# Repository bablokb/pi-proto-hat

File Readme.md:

Pi-Proto-Hat
============

This is a PCB design for a Pi-sized prototyping hat:

The hat has a 40-pin connector for the Pi and exposes most of the GPIOs
on the top and bottom edge. On the left side you will find two connectors
for I2C and one for the UART-pins.

In the middle of the pcb there are two rows with power (5V and 3.3V) and
GND. The pins of the prototyping areas above and below the power-rails
are not connected.

In the directory `kicad/pi-proto-hat` you will find the complete
KiCAD project for the hat. The hat has been successfully produced
(by JLCpcb.com).

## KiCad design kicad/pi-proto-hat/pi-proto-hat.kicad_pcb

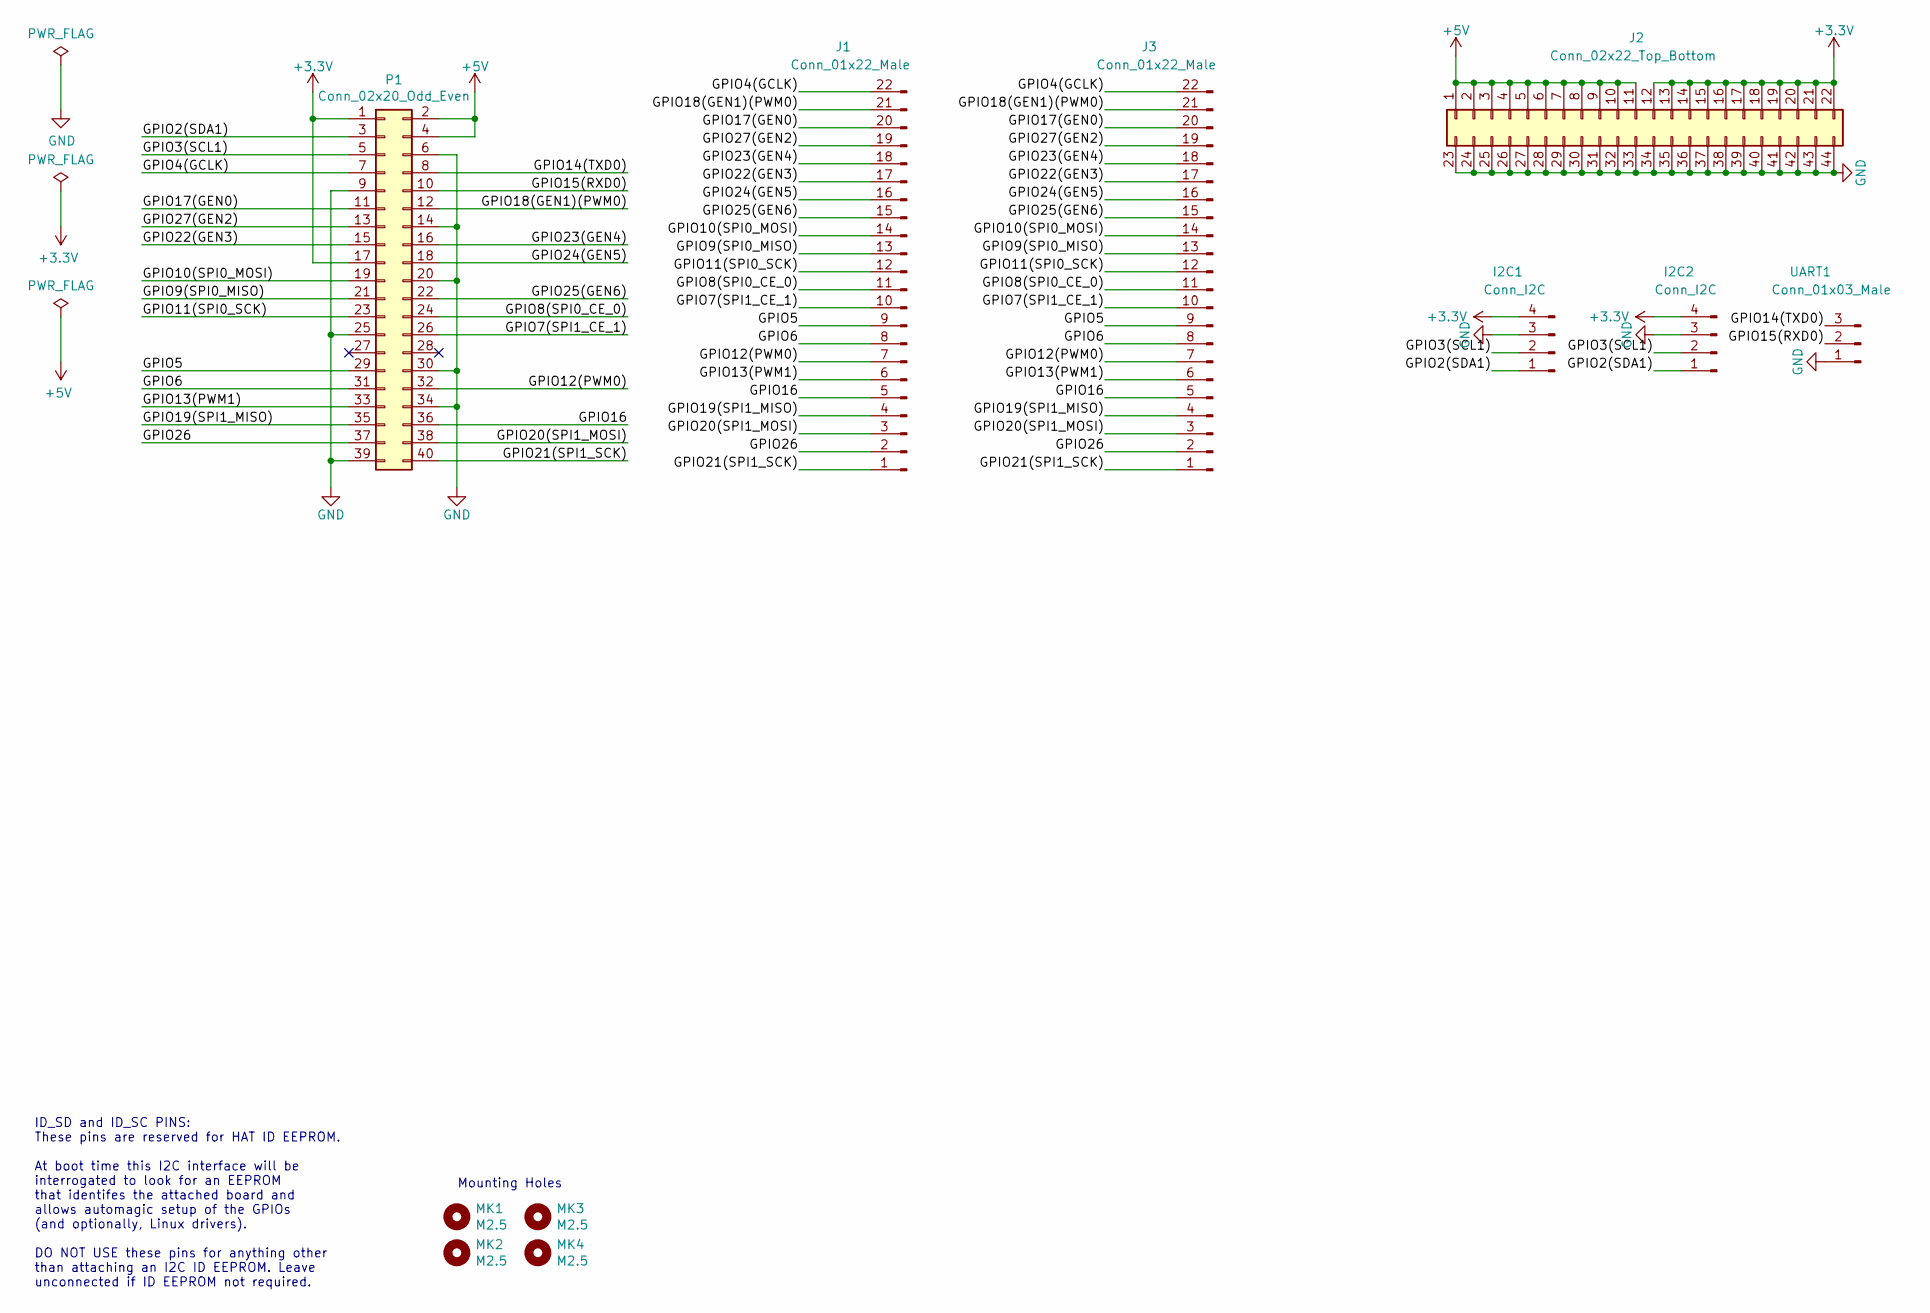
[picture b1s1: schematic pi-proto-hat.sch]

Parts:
I2C1, I2C2: Conn_I2C; Proto_Area_04x01
J1, J3: Conn_01x22_Male; Proto_Area_22x01
J2: Conn_02x22_Top_Bottom; Proto_Area_22x02
MK1, MK2, MK3, MK4: M2.5; MountingHole_2.7mm_M2.5
P1: Conn_02x20_Odd_Even; PinSocket_2x20_P2.54mm_Vertical
UART1: Conn_01x03_Male; Proto_Area_03x01

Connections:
+3V3: I2C1.4, I2C2.4, J2.12, J2.13, J2.14, J2.15, J2.16, J2.17, J2.18, J2.19, J2.20, J2.21, J2.22, P1.1, P1.17
+5V: J2.1, J2.2, J2.3, J2.4, J2.5, J2.6, J2.7, J2.8, J2.9, J2.10, J2.11, P1.2, P1.4
/GPIO2(SDA1): I2C1.1, I2C2.1, P1.3
/GPIO3(SCL1): I2C1.2, I2C2.2, P1.5
/GPIO4(GCLK): J1.22, J3.22, P1.7
/GPIO5: J1.9, J3.9, P1.29
/GPIO6: J1.8, J3.8, P1.31
/GPIO7(SPI1_CE_1): J1.10, J3.10, P1.26
/GPIO8(SPI0_CE_0): J1.11, J3.11, P1.24
/GPIO9(SPI0_MISO): J1.13, J3.13, P1.21
/GPIO10(SPI0_MOSI): J1.14, J3.14, P1.19
/GPIO11(SPI0_SCK): J1.12, J3.12, P1.23
/GPIO12(PWM0): J1.7, J3.7, P1.32
/GPIO13(PWM1): J1.6, J3.6, P1.33
/GPIO14(TXD0): P1.8, UART1.3
/GPIO15(RXD0): P1.10, UART1.2
/GPIO16: J1.5, J3.5, P1.36
/GPIO17(GEN0): J1.20, J3.20, P1.11
/GPIO18(GEN1)(PWM0): J1.21, J3.21, P1.12
/GPIO19(SPI1_MISO): J1.4, J3.4, P1.35
/GPIO20(SPI1_MOSI): J1.3, J3.3, P1.38
/GPIO21(SPI1_SCK): J1.1, J3.1, P1.40
/GPIO22(GEN3): J1.17, J3.17, P1.15
/GPIO23(GEN4): J1.18, J3.18, P1.16
/GPIO24(GEN5): J1.16, J3.16, P1.18
/GPIO25(GEN6): J1.15, J3.15, P1.22
/GPIO26: J1.2, J3.2, P1.37
/GPIO27(GEN2): J1.19, J3.19, P1.13
GND: I2C1.3, I2C2.3, J2.23, J2.24, J2.25, J2.26, J2.27, J2.28, J2.29, J2.30, J2.31, J2.32, J2.33, J2.34, J2.35, J2.36, J2.37, J2.38, J2.39, J2.40, J2.41, J2.42, J2.43, J2.44, P1.6, P1.9, P1.14, P1.20, P1.25, P1.30, P1.34, P1.39, UART1.1

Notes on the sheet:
ID_SD and ID_SC PINS: These pins are reserved for HAT ID EEPROM. At boot time this I2C interface will be interrogated to look for an EEPROM that identifes the attached board and allows automagic setup of the GPIOs (and optionally, Linux drivers). DO NOT USE these pins for anything other than attach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
Mounting Holes

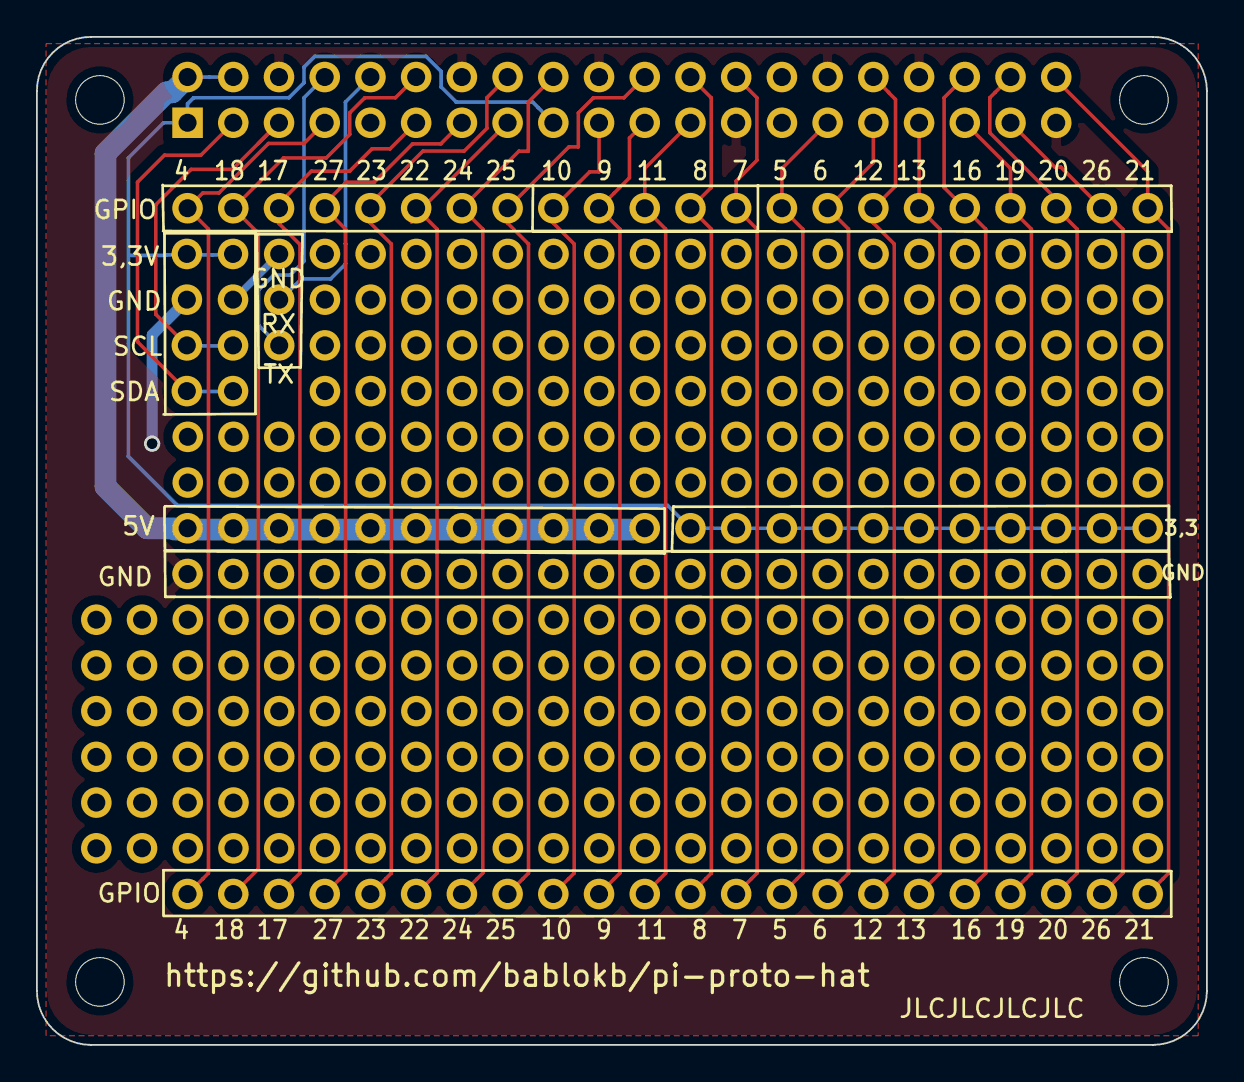
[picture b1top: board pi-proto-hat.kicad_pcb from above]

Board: 2 copper layers, 65.0 x 56.0 mm, 11 parts (1 on the bottom side), 29 nets.

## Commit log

2020-01-30 R1: one GPIO connector, one I2C connector
2020-02-15 R2: 1xUART+GND, 2xI2C+VCC+GND
2020-02-15 R3: VCC+GND connector 22x02
2020-02-17 changed footprints, added two prototype-areas
2020-02-21 added routing for second GPIO connector
2020-02-21 changed/added prototyping areas to fill pcb
2020-02-22 removed unnecessary trace / configured gerber-plot
2020-04-10 minor changes (resolution, removed borders)
